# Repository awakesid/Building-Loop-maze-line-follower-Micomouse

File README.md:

# Building-Loop-maze-line-follower-Micomouse

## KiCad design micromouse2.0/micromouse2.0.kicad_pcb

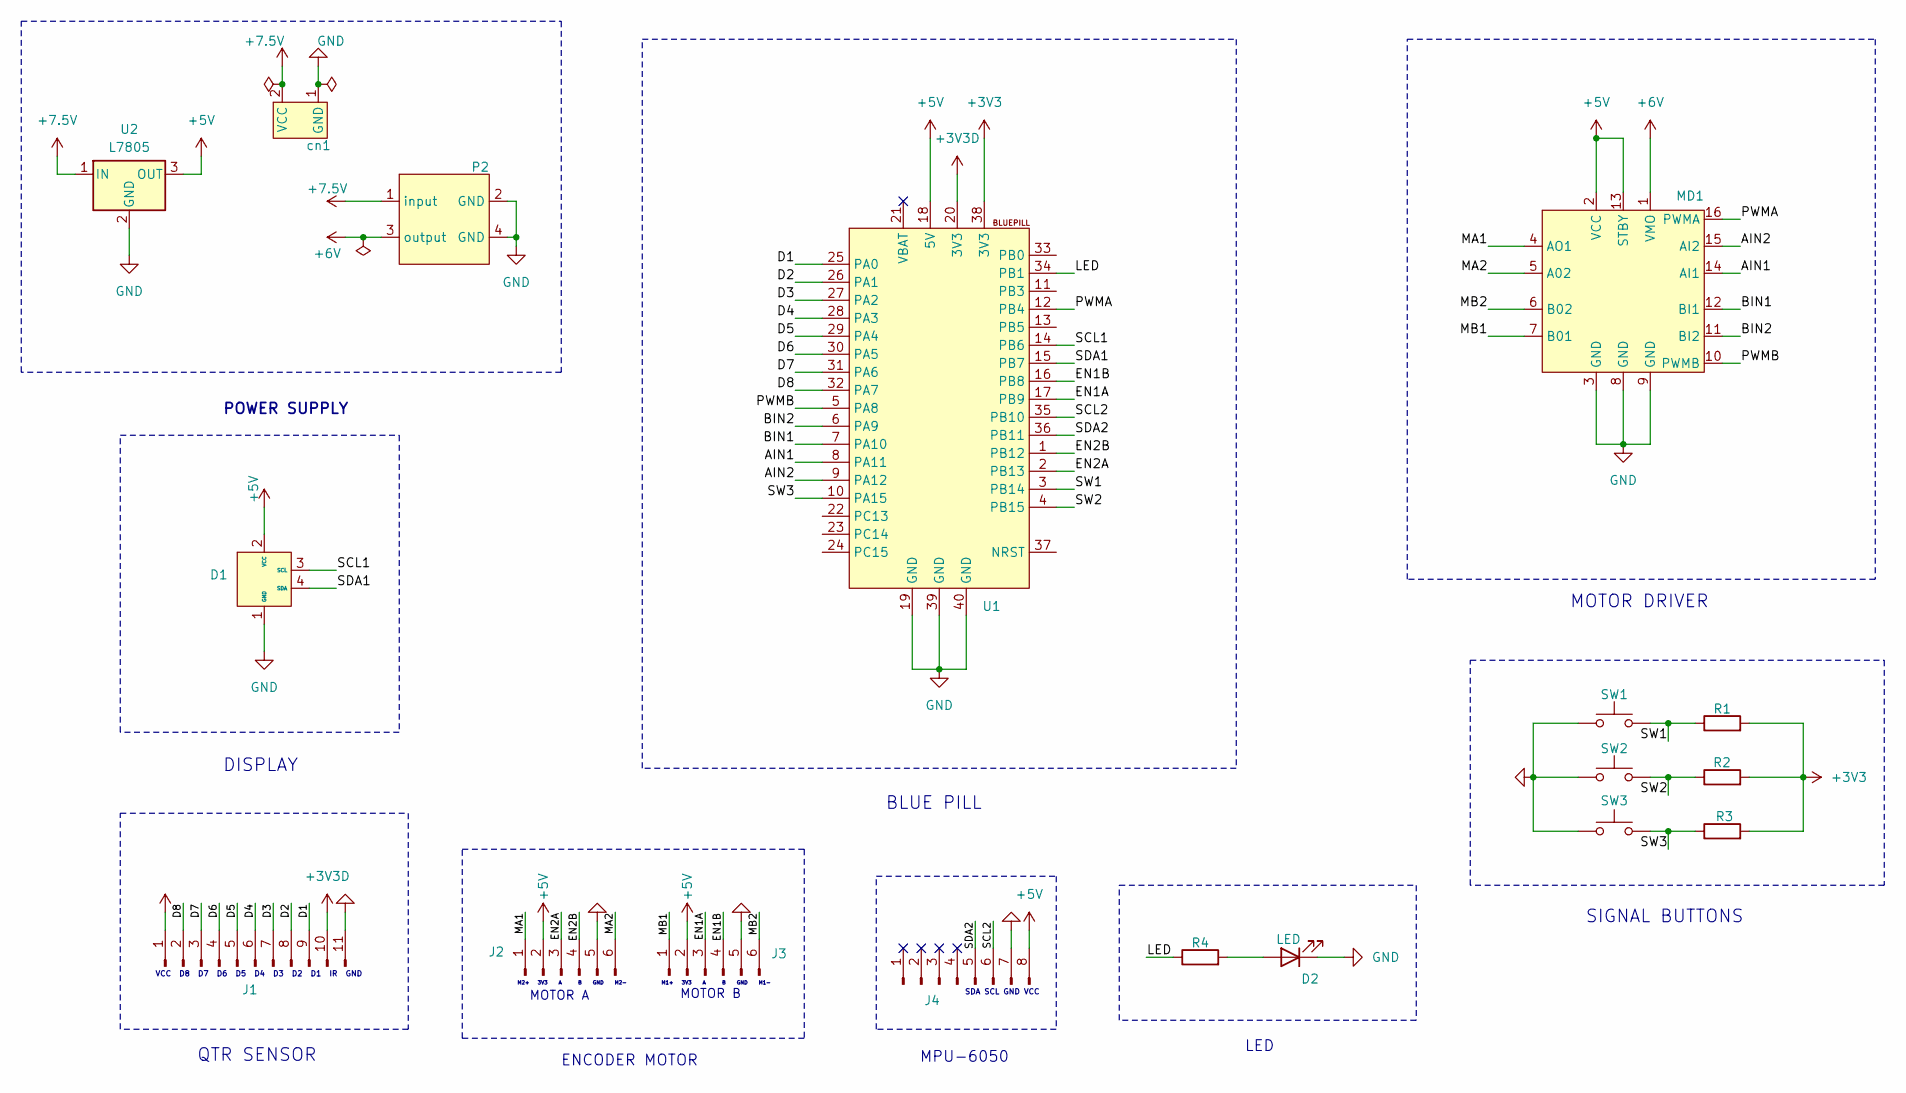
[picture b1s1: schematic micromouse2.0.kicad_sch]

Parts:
D1: 128*32 spi display
D2: LED; LED_D3.0mm
J1: Conn_01x11_Pin; PinHeader_1x11_P2.54mm_Vertical
J2, J3: Conn_01x06_Pin; PinSocket_1x06_P2.54mm_Vertical
J4: Conn_01x08_Pin; PinHeader_1x08_P2.54mm_Vertical
MD1: TB6612FNG motor driver
P2: buck converter
R1, R2, R3, R4: R; R_Axial_DIN0204_L3.6mm_D1.6mm_P5.08mm_Horizontal
SW1, SW2, SW3: SW_Push; SW_PUSH_6mm
U1: bluepill
U2: L7805; TO-220-3_Vertical
cn1: PinSocket_1x02_P2.54mm_Vertical

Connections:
+3V3: J1.1, R1.2, R2.2, R3.2, U1.38 (3V3)
+3V3D: J1.10, U1.20 (3V3)
+5V: D1.2 (VCC), J2.2, J3.2, J4.8, MD1.2 (VCC), MD1.13 (STBY), U1.18 (5V), U2.3 (OUT)
+6V: MD1.1 (VMO), P2.3 (output)
+7.5V: P2.1 (input), U2.1 (IN), cn1.2 (VCC)
/AIN1: MD1.14 (AI1), U1.8 (PA11)
/AIN2: MD1.15 (AI2), U1.9 (PA12)
/BIN1: MD1.12 (BI1), U1.7 (PA10)
/BIN2: MD1.11 (BI2), U1.6 (PA9)
/D1: J1.9, U1.25 (PA0)
/D2: J1.8, U1.26 (PA1)
/D3: J1.7, U1.27 (PA2)
/D4: J1.6, U1.28 (PA3)
/D5: J1.5, U1.29 (PA4)
/D6: J1.4, U1.30 (PA5)
/D7: J1.3, U1.31 (PA6)
/D8: J1.2, U1.32 (PA7)
/EN1A: J3.3, U1.17 (PB9)
/EN1B: J3.4, U1.16 (PB8)
/EN2A: J2.3, U1.2 (PB13)
/EN2B: J2.4, U1.1 (PB12)
/LED: R4.1, U1.34 (PB1)
/MA1: J2.1, MD1.4 (AO1)
/MA2: J2.6, MD1.5 (A02)
/MB1: J3.1, MD1.7 (B01)
/MB2: J3.6, MD1.6 (B02)
/PWMA: MD1.16 (PWMA), U1.12 (PB4)
/PWMB: MD1.10 (PWMB), U1.5 (PA8)
/SCL1: D1.3 (SCL), U1.14 (PB6)
/SCL2: J4.6, U1.35 (PB10)
/SDA1: D1.4 (SDA), U1.15 (PB7)
/SDA2: J4.5, U1.36 (PB11)
/SW1: R1.1, SW1.2, U1.3 (PB14)
/SW2: R2.1, SW2.2, U1.4 (PB15)
/SW3: R3.1, SW3.2, U1.10 (PA15)
GND: D1.1 (GND), D2.1 (K), J1.11, J2.5, J3.5, J4.7, MD1.3 (GND), MD1.8 (GND), MD1.9 (GND), P2.2 (GND), P2.4 (GND), SW1.1, SW2.1, SW3.1, U1.19 (GND), U1.39 (GND), U1.40 (GND), U2.2 (GND), cn1.1 (GND)
unnamed: D2.2 (A), R4.2

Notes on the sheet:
SIGNAL BUTTONS
MOTOR B
QTR SENSOR
DISPLAY
ENCODER MOTOR
LED
MPU-6050
SDA SCL GND VCC
M1+ 3V3 A B GND M1-
MOTOR DRIVER
VCC D8 D7 D6 D5 D4 D3 D2 D1 IR GND
M2+ 3V3 A B GND M2-
MOTOR A
POWER SUPPLY
BLUE PILL

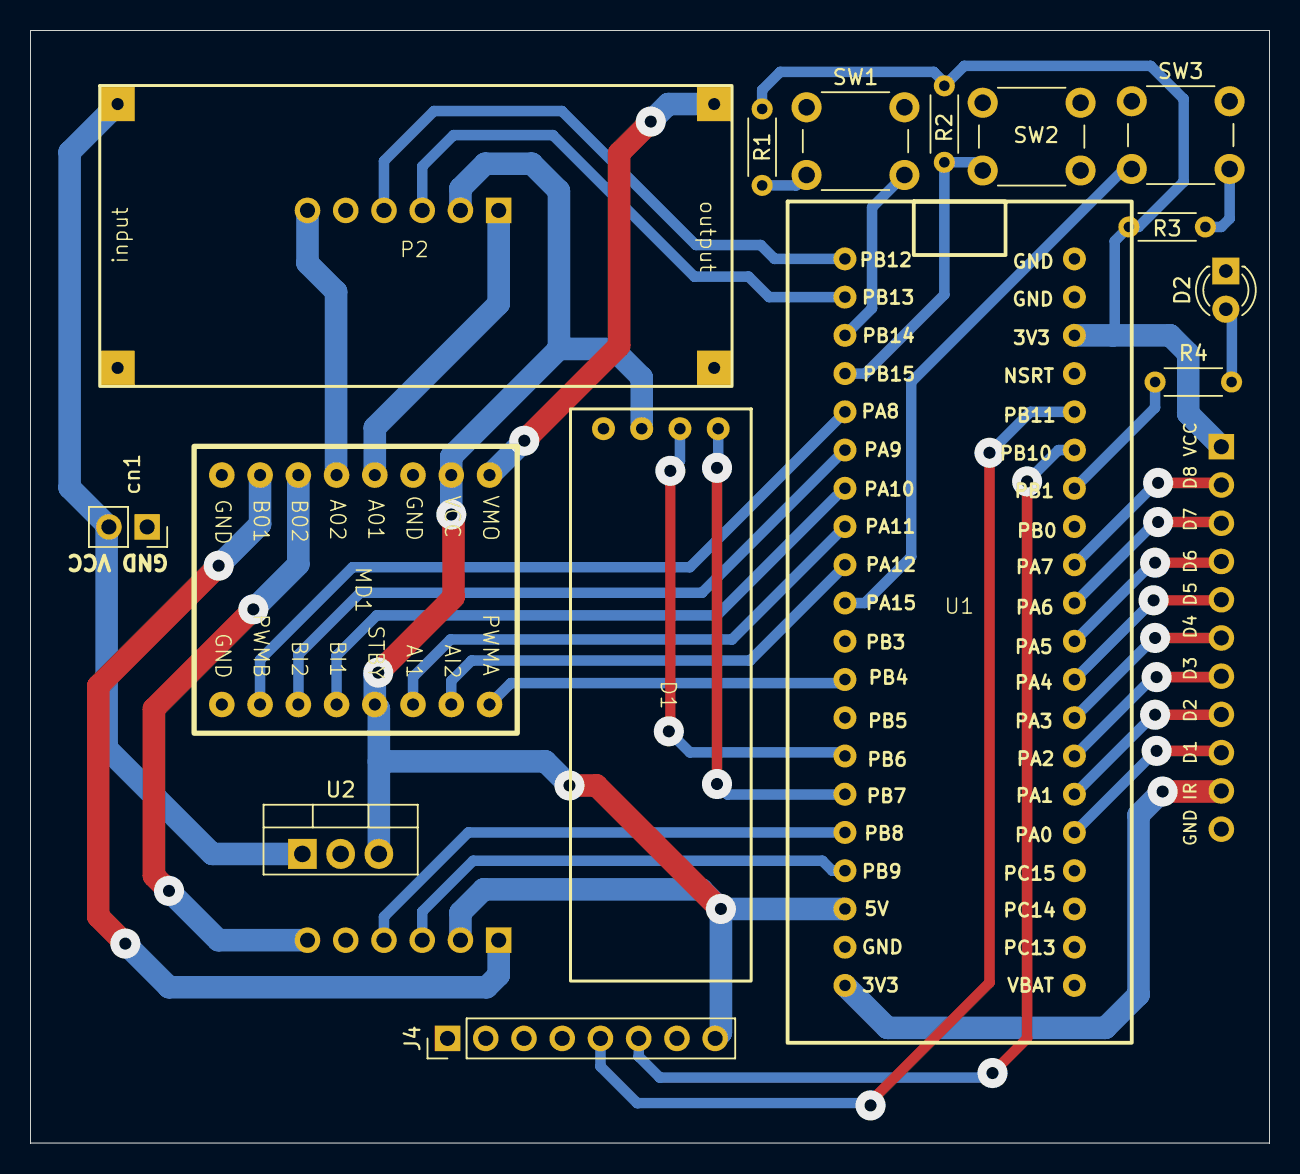
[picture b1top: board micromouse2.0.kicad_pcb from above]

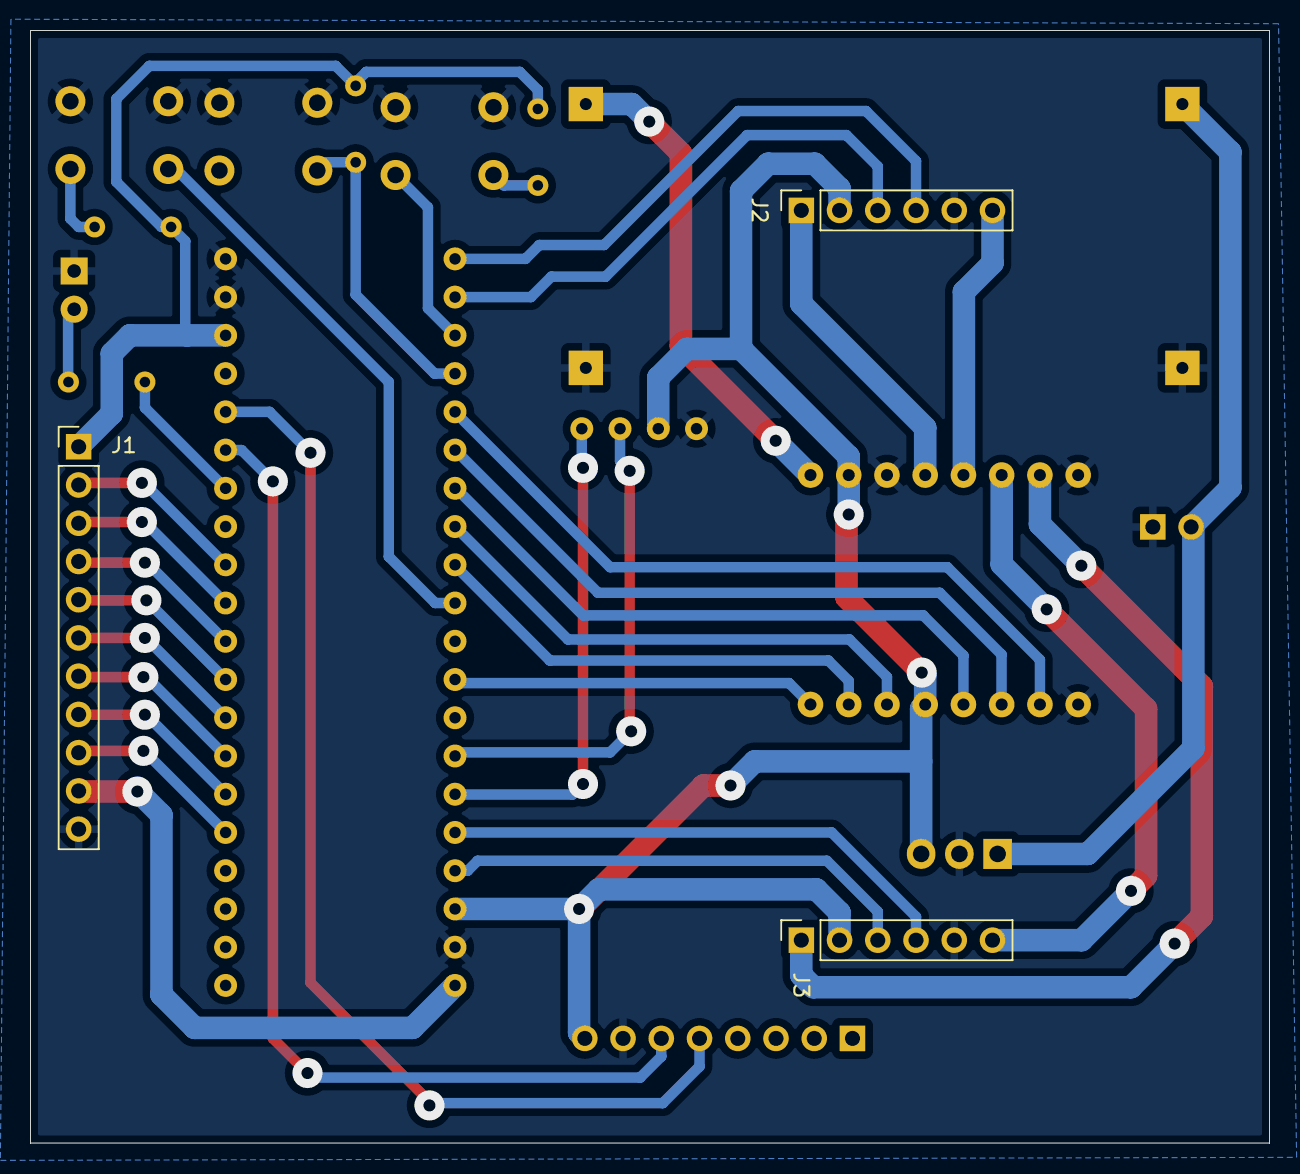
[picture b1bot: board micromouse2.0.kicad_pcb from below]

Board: 2 copper layers, 82.3 x 73.9 mm, 18 parts (3 on the bottom side), 37 nets.

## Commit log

2024-06-10 added
2024-06-11 added about reop
2024-06-11 updated chasis
2024-06-11 change
2024-06-11 chnages
2024-07-21 pcb design
